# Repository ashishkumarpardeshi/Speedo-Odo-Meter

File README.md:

# Speedo-Odo-Meter

## Open Source Hardware instructional project by the Homi Bhabha Centre for Science Education, Mumbai
* [Discussion Forum](https://metastudio.org/t/lets-build-speedo-odo-meter-for-your-bicycle/4850)

License
-------
[CERN Open Hardware Licence v1.2 ]

[CERN Open Hardware Licence v1.2 ]:http://www.ohwr.org/attachments/2388/cern_ohl_v_1_2.txt

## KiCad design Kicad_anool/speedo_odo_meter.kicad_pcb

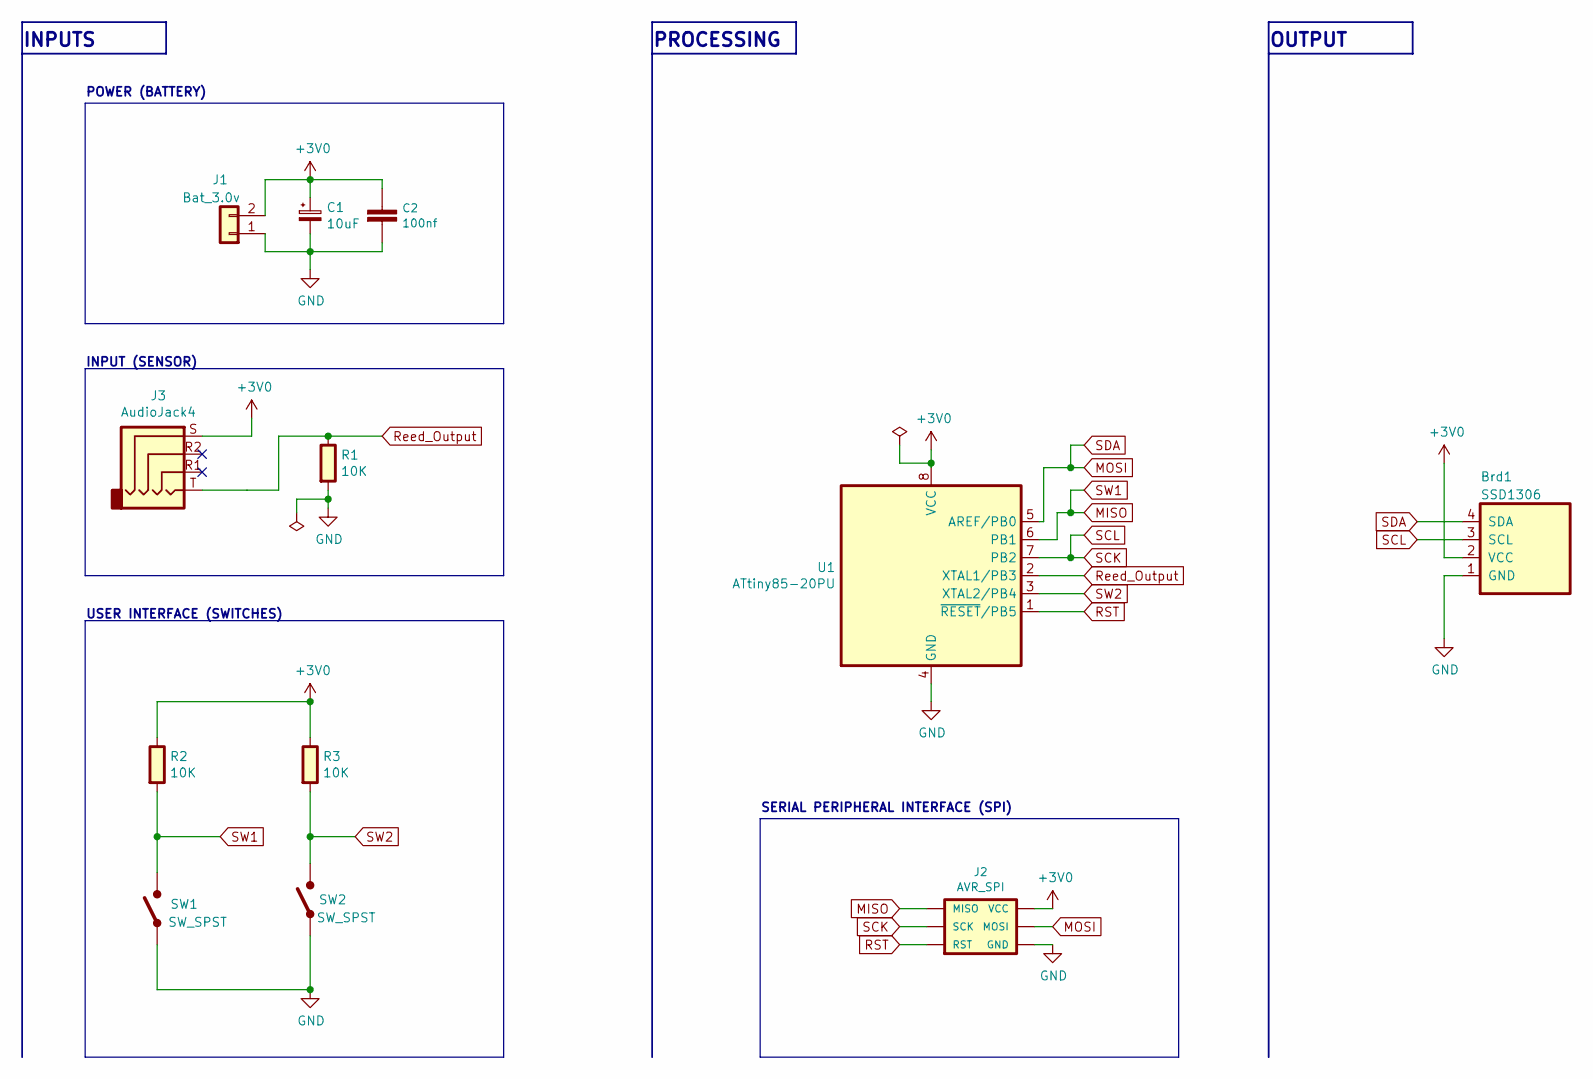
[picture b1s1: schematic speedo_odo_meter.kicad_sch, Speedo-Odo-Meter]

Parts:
Brd1: SSD1306; 128x64OLED
C1: 10uF; CP_Radial_D8.0mm_P2.50mm
C2: 100nf; C_Disc_D3.8mm_W2.6mm_P2.50mm
J1: Bat_3.0v; JST_PH_S2B-PH-K_1x02_P2.00mm_Horizontal
J2: AVR_SPI; PinHeader_2x03_P2.54mm_Vertical
J3: AudioJack4; Jack_3.5mm_PJ320E_Horizontal
R1, R2, R3: 10K; R_Axial_DIN0207_L6.3mm_D2.5mm_P7.62mm_Horizontal
SW1, SW2: SW_SPST; SW_PUSH_6mm
U1: ATtiny85-20PU; DIP-8_W7.62mm

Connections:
+3V0: Brd1.2 (VCC), C1.1, C2.1, J1.2, J2.2 (VCC), J3.S, R2.1, R3.1, U1.8 (VCC)
GND: Brd1.1 (GND), C1.2, C2.2, J1.1, J2.6 (GND), R1.2, SW1.1 (A), SW2.1 (A), U1.4 (GND); also elsewhere on the board
MISO: J2.1 (MISO), R2.2, SW1.2 (B), U1.6 (PB1)
MOSI: Brd1.4 (SDA), J2.4 (MOSI), U1.5 (AREF/PB0)
RST: J2.5 (RST), U1.1 (~RESET~/PB5)
Reed_Output: J3.T, R1.1, U1.2 (XTAL1/PB3); also elsewhere on the board
SCK: Brd1.3 (SCL), J2.3 (SCK), U1.7 (PB2)
SW2: R3.2, SW2.2 (B), U1.3 (XTAL2/PB4)

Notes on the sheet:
INPUTS
POWER (BATTERY)
INPUT (SENSOR)
USER INTERFACE (SWITCHES)
PROCESSING
SERIAL PERIPHERAL INTERFACE (SPI)
OUTPUT

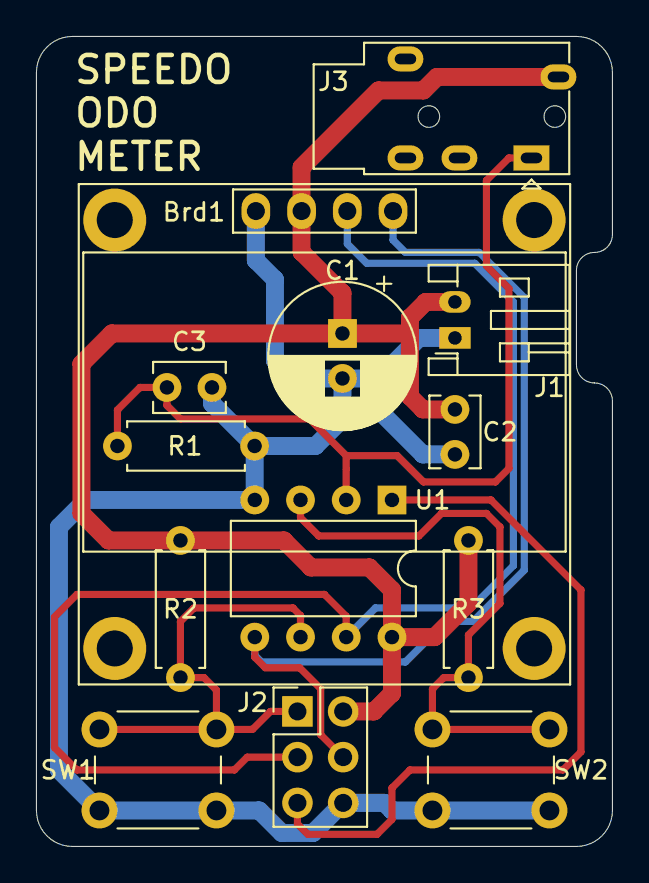
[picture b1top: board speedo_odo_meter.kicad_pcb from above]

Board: 2 copper layers, 32.0 x 45.0 mm, 13 parts (0 on the bottom side), 8 nets.

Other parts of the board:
C3: 100nf; C_Disc_D3.8mm_W2.6mm_P2.50mm

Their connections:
GND: C3.2; also elsewhere on the board
Reed_Output: C3.1; also elsewhere on the board

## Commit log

2020-10-10 cleaned up project
2020-10-11 schematic and PCB layout complete
